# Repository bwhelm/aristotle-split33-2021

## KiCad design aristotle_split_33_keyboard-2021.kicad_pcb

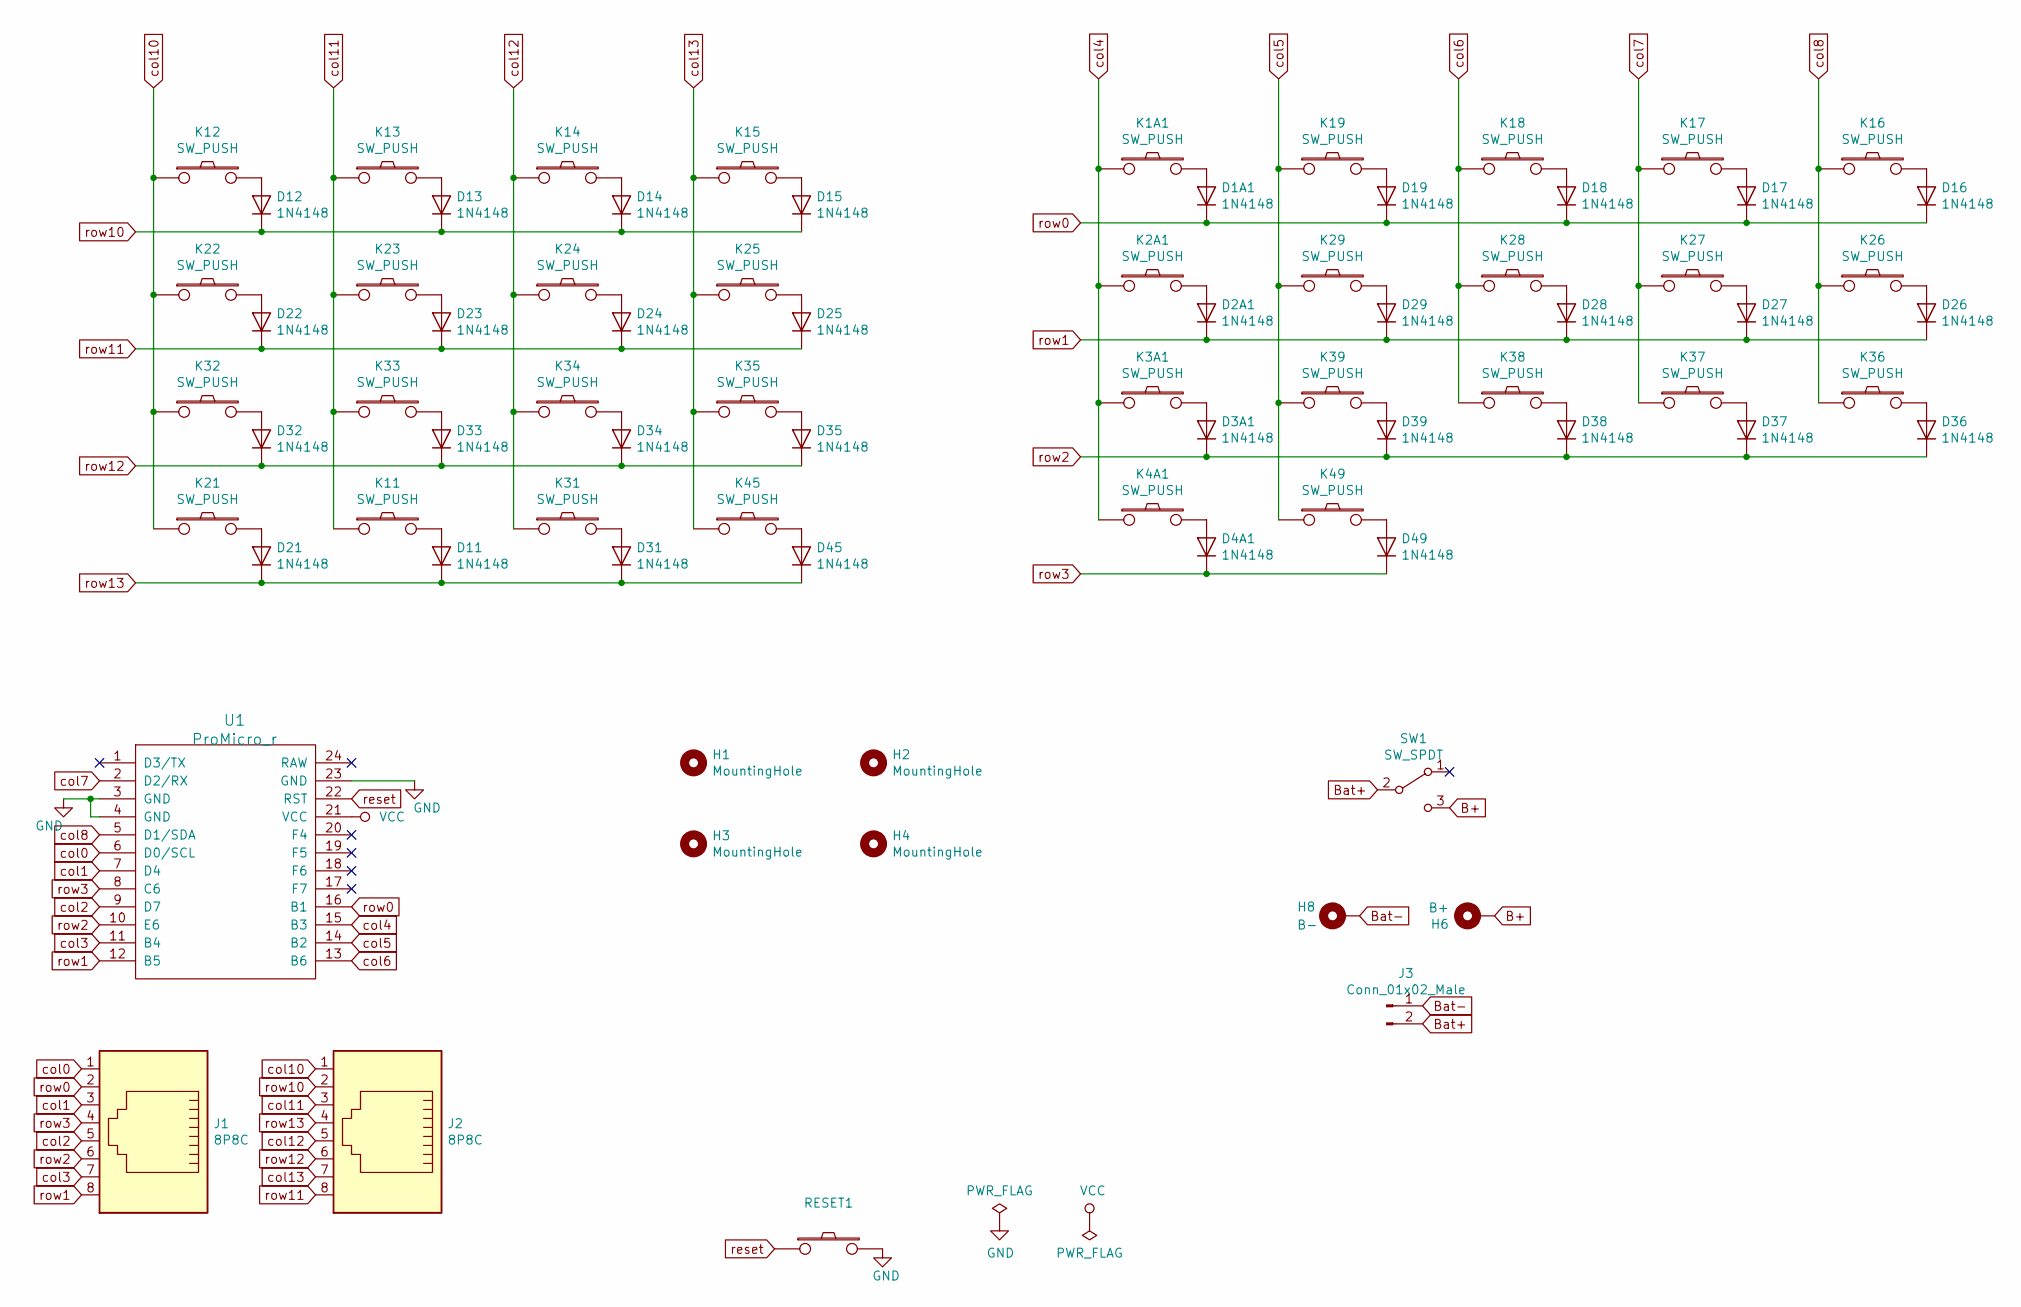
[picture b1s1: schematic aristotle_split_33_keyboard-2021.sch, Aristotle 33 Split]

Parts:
D1A1, D2A1, D3A1, D4A1, D11, D12, D13, D14, D15, D16, D17, D18, D19, D21, D22, D23, D24, D25, D26, D27, D28, D29, D31, D32, D33, D34, D35, D36, D37, D38, D39, D45, D49: 1N4148; D_T-1_P5.08mm_Horizontal-NO_B.SILK
H1, H2, H3, H4: MountingHole; MountingHole_6mm
H6: B+; PinHeader_1x01_P2.54mm_Vertical
H8: B-; PinHeader_1x01_P2.54mm_Vertical
J1, J2: 8P8C; RJ45_Amphenol_54602-x08_Horizontal
J3: Conn_01x02_Male; PinHeader_1x02_P2.54mm_Vertical_SMD_Pin1Left
K1A1, K2A1, K3A1, K4A1, K11, K12, K13, K14, K15, K16, K17, K18, K19, K21, K22, K23, K24, K25, K26, K27, K28, K29, K31, K32, K33, K34, K35, K36, K37, K38, K39, K45, K49: SW_PUSH; Kailh-Choc_1350-Keyswitch-NONREVERSIBLE
RESET1: SW_PUSH_6mm
SW1: SW_SPDT; SW_CuK_OS102011MA1QN1_SPDT_Angled
U1: ProMicro_r; ProMicro

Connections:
B+: H6.1, SW1.3 (C)
Bat+: J3.2, SW1.2 (B)
Bat-: H8.1, J3.1
GND: RESET1.2, U1.3 (GND), U1.4 (GND), U1.23 (GND)
unnamed: D1A1.2 (A), K1A1.2
unnamed: D2A1.2 (A), K2A1.2
unnamed: D3A1.2 (A), K3A1.2
unnamed: D4A1.2 (A), K4A1.2
unnamed: D11.2 (A), K11.2
unnamed: D12.2 (A), K12.2
unnamed: D13.2 (A), K13.2
unnamed: D14.2 (A), K14.2
unnamed: D15.2 (A), K15.2
unnamed: D16.2 (A), K16.2
unnamed: D17.2 (A), K17.2
unnamed: D18.2 (A), K18.2
unnamed: D19.2 (A), K19.2
unnamed: D21.2 (A), K21.2
unnamed: D22.2 (A), K22.2
unnamed: D23.2 (A), K23.2
unnamed: D24.2 (A), K24.2
unnamed: D25.2 (A), K25.2
unnamed: D26.2 (A), K26.2
unnamed: D27.2 (A), K27.2
unnamed: D28.2 (A), K28.2
unnamed: D29.2 (A), K29.2
unnamed: D31.2 (A), K31.2
unnamed: D32.2 (A), K32.2
unnamed: D33.2 (A), K33.2
unnamed: D34.2 (A), K34.2
unnamed: D35.2 (A), K35.2
unnamed: D36.2 (A), K36.2
unnamed: D37.2 (A), K37.2
unnamed: D38.2 (A), K38.2
unnamed: D39.2 (A), K39.2
unnamed: D45.2 (A), K45.2
unnamed: D49.2 (A), K49.2
col0: J1.1, U1.6 (D0/SCL)
col1: J1.3, U1.7 (D4)
col2: J1.5, U1.9 (D7)
col3: J1.7, U1.11 (B4)
col4: K1A1.1, K2A1.1, K3A1.1, K4A1.1, U1.15 (B3)
col5: K19.1, K29.1, K39.1, K49.1, U1.14 (B2)
col6: K18.1, K28.1, K38.1, U1.13 (B6)
col7: K17.1, K27.1, K37.1, U1.2 (D2/RX)
col8: K16.1, K26.1, K36.1, U1.5 (D1/SDA)
col10: J2.1, K12.1, K21.1, K22.1, K32.1
col11: J2.3, K11.1, K13.1, K23.1, K33.1
col12: J2.5, K14.1, K24.1, K31.1, K34.1
col13: J2.7, K15.1, K25.1, K35.1, K45.1
reset: RESET1.1, U1.22 (RST)
row0: D1A1.1 (K), D16.1 (K), D17.1 (K), D18.1 (K), D19.1 (K), J1.2, U1.16 (B1)
row1: D2A1.1 (K), D26.1 (K), D27.1 (K), D28.1 (K), D29.1 (K), J1.8, U1.12 (B5)
row2: D3A1.1 (K), D36.1 (K), D37.1 (K), D38.1 (K), D39.1 (K), J1.6, U1.10 (E6)
row3: D4A1.1 (K), D49.1 (K), J1.4, U1.8 (C6)
row10: D12.1 (K), D13.1 (K), D14.1 (K), D15.1 (K), J2.2
row11: D22.1 (K), D23.1 (K), D24.1 (K), D25.1 (K), J2.8
row12: D32.1 (K), D33.1 (K), D34.1 (K), D35.1 (K), J2.6
row13: D11.1 (K), D21.1 (K), D31.1 (K), D45.1 (K), J2.4

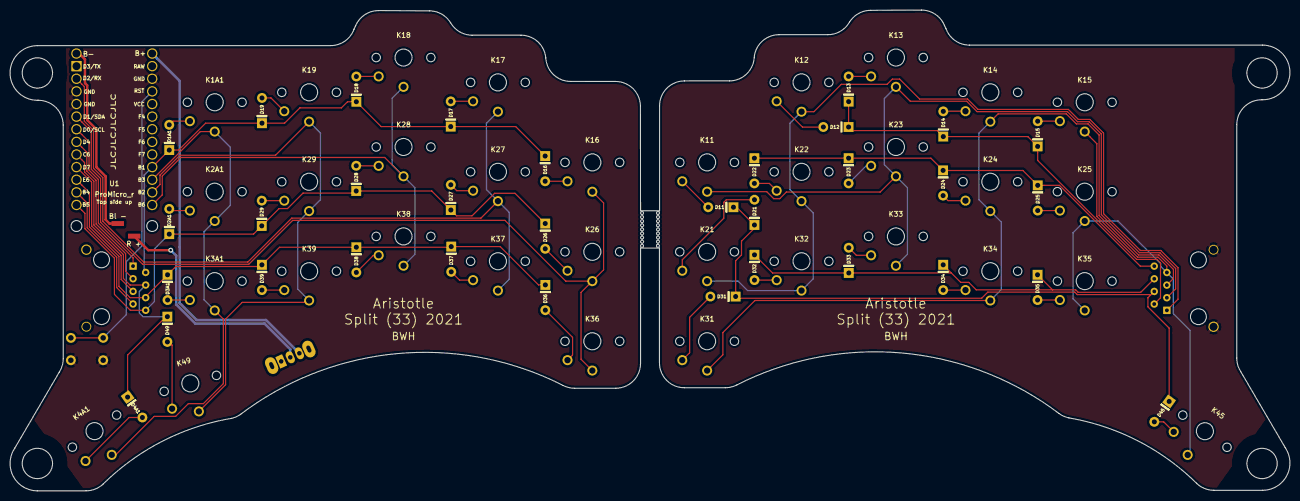
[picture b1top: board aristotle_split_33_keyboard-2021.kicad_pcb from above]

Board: 2 copper layers, 257.6 x 96.8 mm, 82 parts (0 on the bottom side), 59 nets.

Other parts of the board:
1, 2: MountingHole_2.2mm_M2
breakaway: Stamp_Holes_7.5mm
breakaway#2: Stamp_Holes_7.5mm

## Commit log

2021-08-19 Create case
